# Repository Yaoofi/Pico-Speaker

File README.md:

# Pico Speaker

# Description
This is my first try to make use of Raspberry Pi Pico

# Screenshots

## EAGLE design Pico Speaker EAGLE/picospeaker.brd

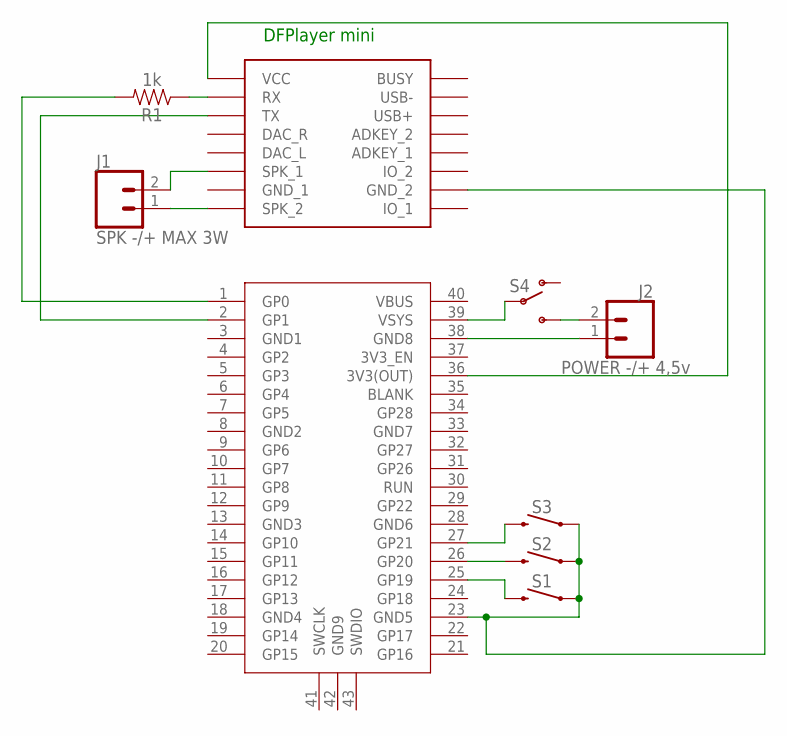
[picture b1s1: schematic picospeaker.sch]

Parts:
J1: SPK -/+ MAX 3W; 1X02
J2: POWER -/+ 4,5v; 1X02
R1: 1k; AXIAL-0.3-KIT
S1, S2, S3: MOMENTARY-SWITCH-SPST-PTH-6.0MM-KIT; TACTILE_SWITCH_PTH_6.0MM_KIT
S4: SWITCH-SPDTSMD; SWITCH_SPDT_SMD
U$1: RASPBERRY-PI-PICO; PICO-PKG-TH
U$2: DFPLAYER

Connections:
GND1: U$1.3 (GND1)
GND2: U$1.8 (GND2)
GND3: U$1.13 (GND3)
GND4: U$1.18 (GND4)
GND6: U$1.28 (GND6)
GND7: U$1.33 (GND7)
GND9: U$1.42 (GND9)
unnamed: R1.P$1 (1), U$2.RX
unnamed: S3.3 (2), U$1.27 (GP21)
unnamed: U$1.36 (3V3(OUT)), U$2.VCC
unnamed: J1.2, U$2.SPK1 (SPK_1)
unnamed: J1.1, U$2.SPK2 (SPK_2)
unnamed: R1.P$2 (2), U$1.1 (GP0)
unnamed: U$1.2 (GP1), U$2.TX
unnamed: S1.1, S2.1, S3.1, U$1.23 (GND5), U$2.GND_2
unnamed: S2.3 (2), U$1.26 (GP20)
unnamed: S1.3 (2), U$1.25 (GP19)
unnamed: S4.2, U$1.39 (VSYS)
unnamed: J2.2, S4.3 (S)
unnamed: J2.1, U$1.38 (GND8)
VBUS: U$1.40 (VBUS)

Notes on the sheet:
DFPlayer mini

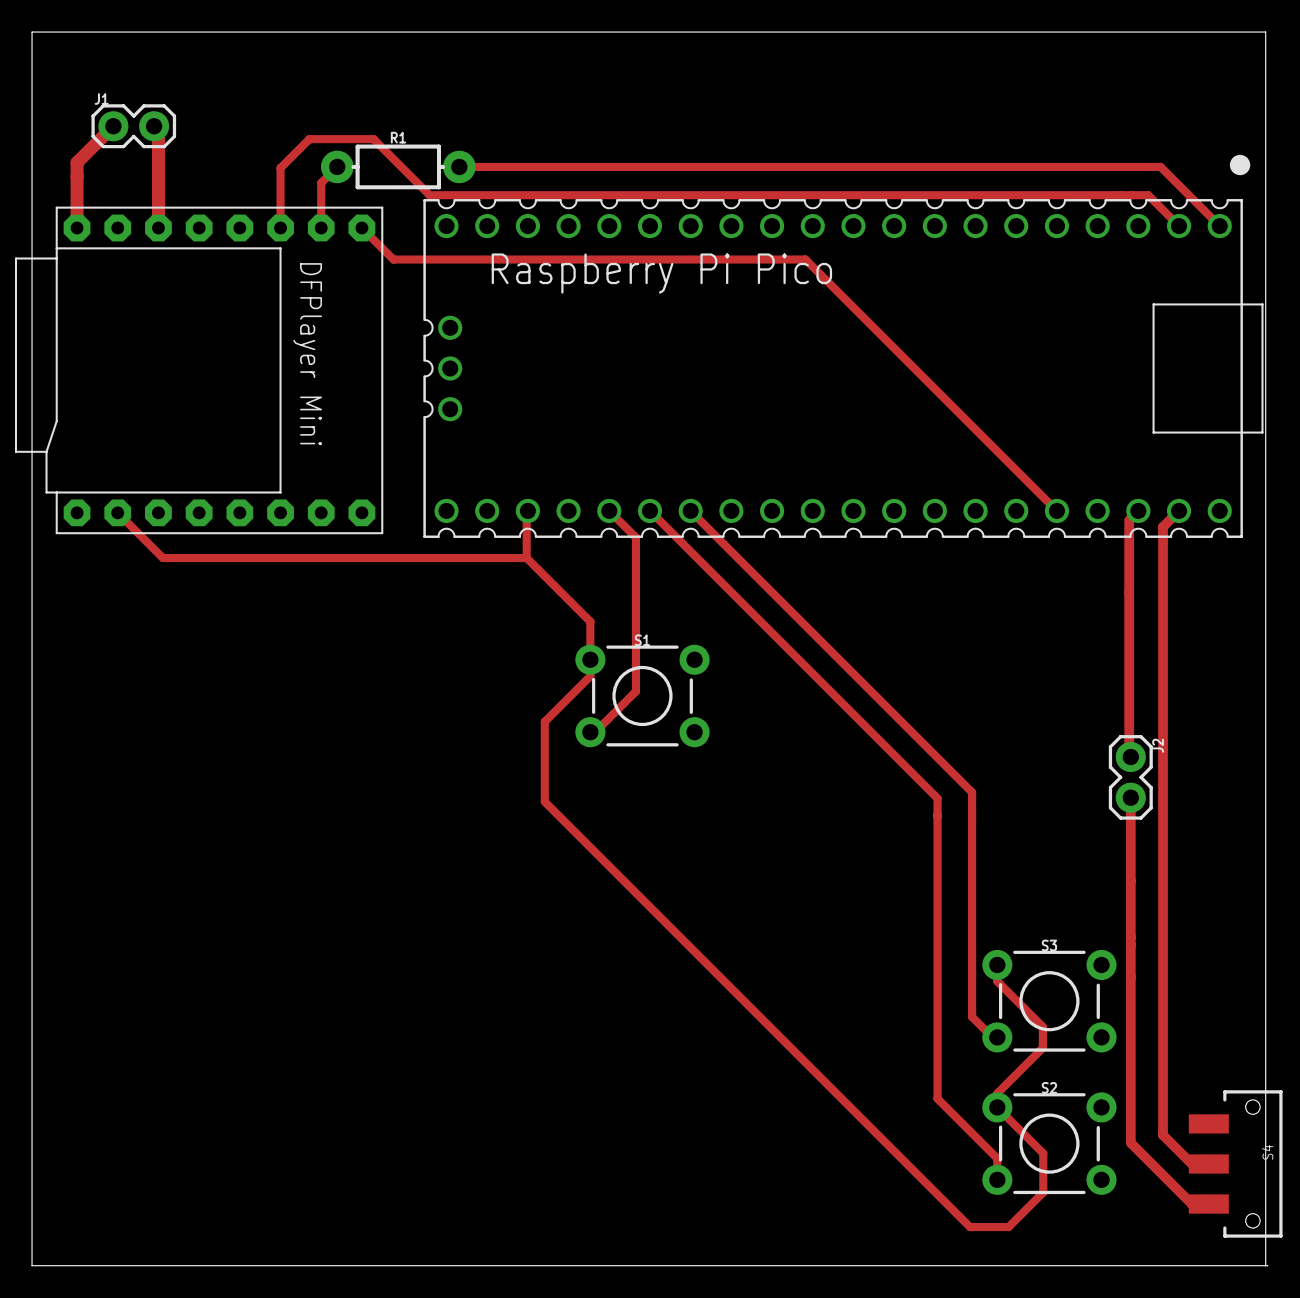
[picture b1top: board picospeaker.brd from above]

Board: 2 copper layers, 77.1 x 77.0 mm, 9 parts (0 on the bottom side), 13 nets.

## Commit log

2023-11-25 1st commit
2023-12-26 Added libs used in Eagle

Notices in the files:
parts and their libraries:
SparkFun-Connectors: Licensing: Creative Commons ShareAlike 4.0 International - https://creativecommons.org/licenses/by-sa/4.0
